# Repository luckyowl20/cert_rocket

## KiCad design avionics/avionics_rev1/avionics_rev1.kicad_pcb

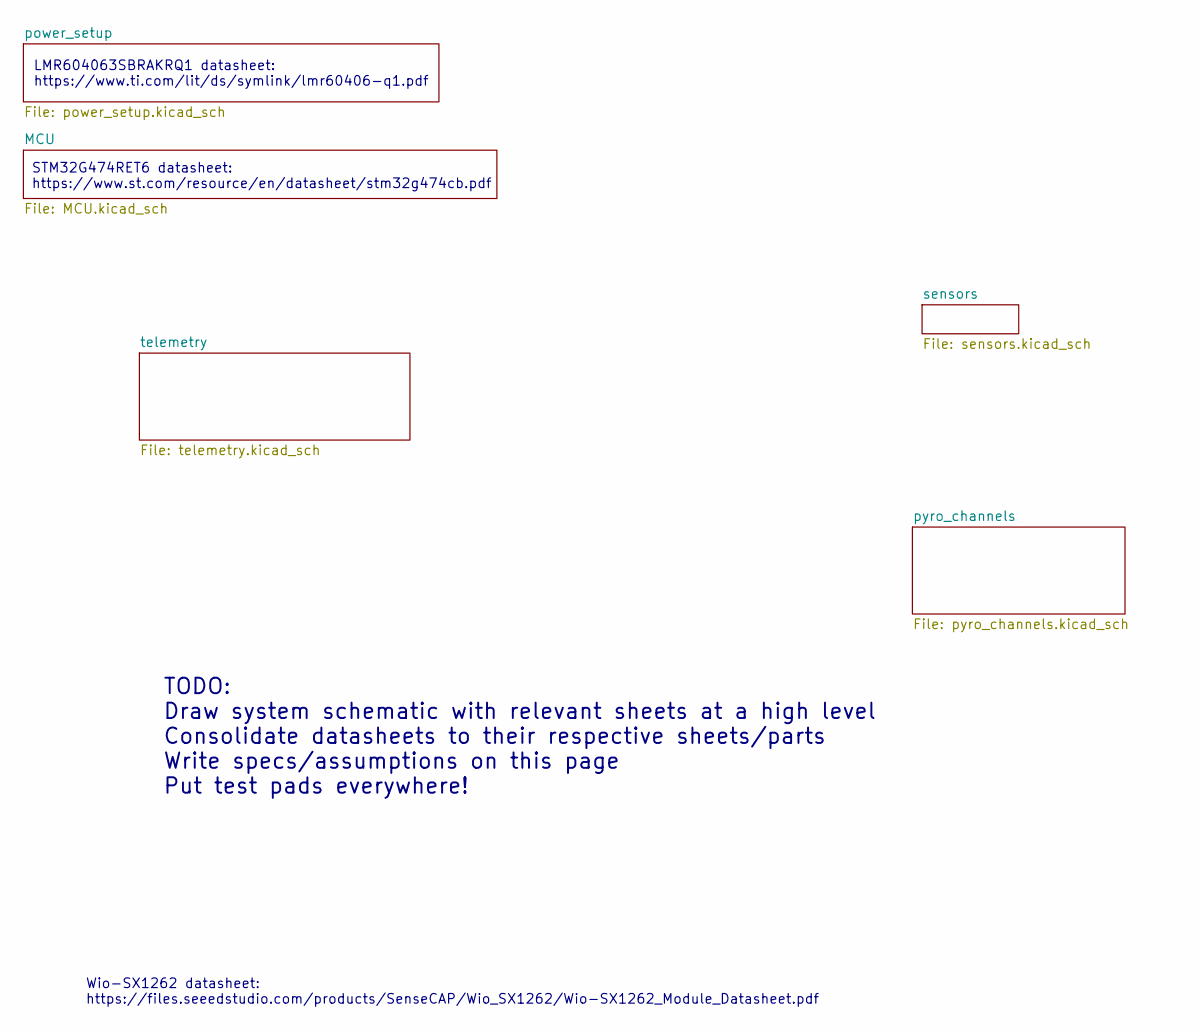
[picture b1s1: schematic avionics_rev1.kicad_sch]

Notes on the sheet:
Wio-SX1262 datasheet: https://files.seeedstudio.com/products/SenseCAP/Wio_SX1262/Wio-SX1262_Module_Datasheet.pdf
STM32G474RET6 datasheet: https://www.st.com/resource/en/datasheet/stm32g474cb.pdf
LMR604063SBRAKRQ1 datasheet: https://www.ti.com/lit/ds/symlink/lmr60406-q1.pdf
TODO: Draw system schematic with relevant sheets at a high level Consolidate datasheets to their respective sheets/parts Write specs/assumptions on this page Put test pads everywhere!

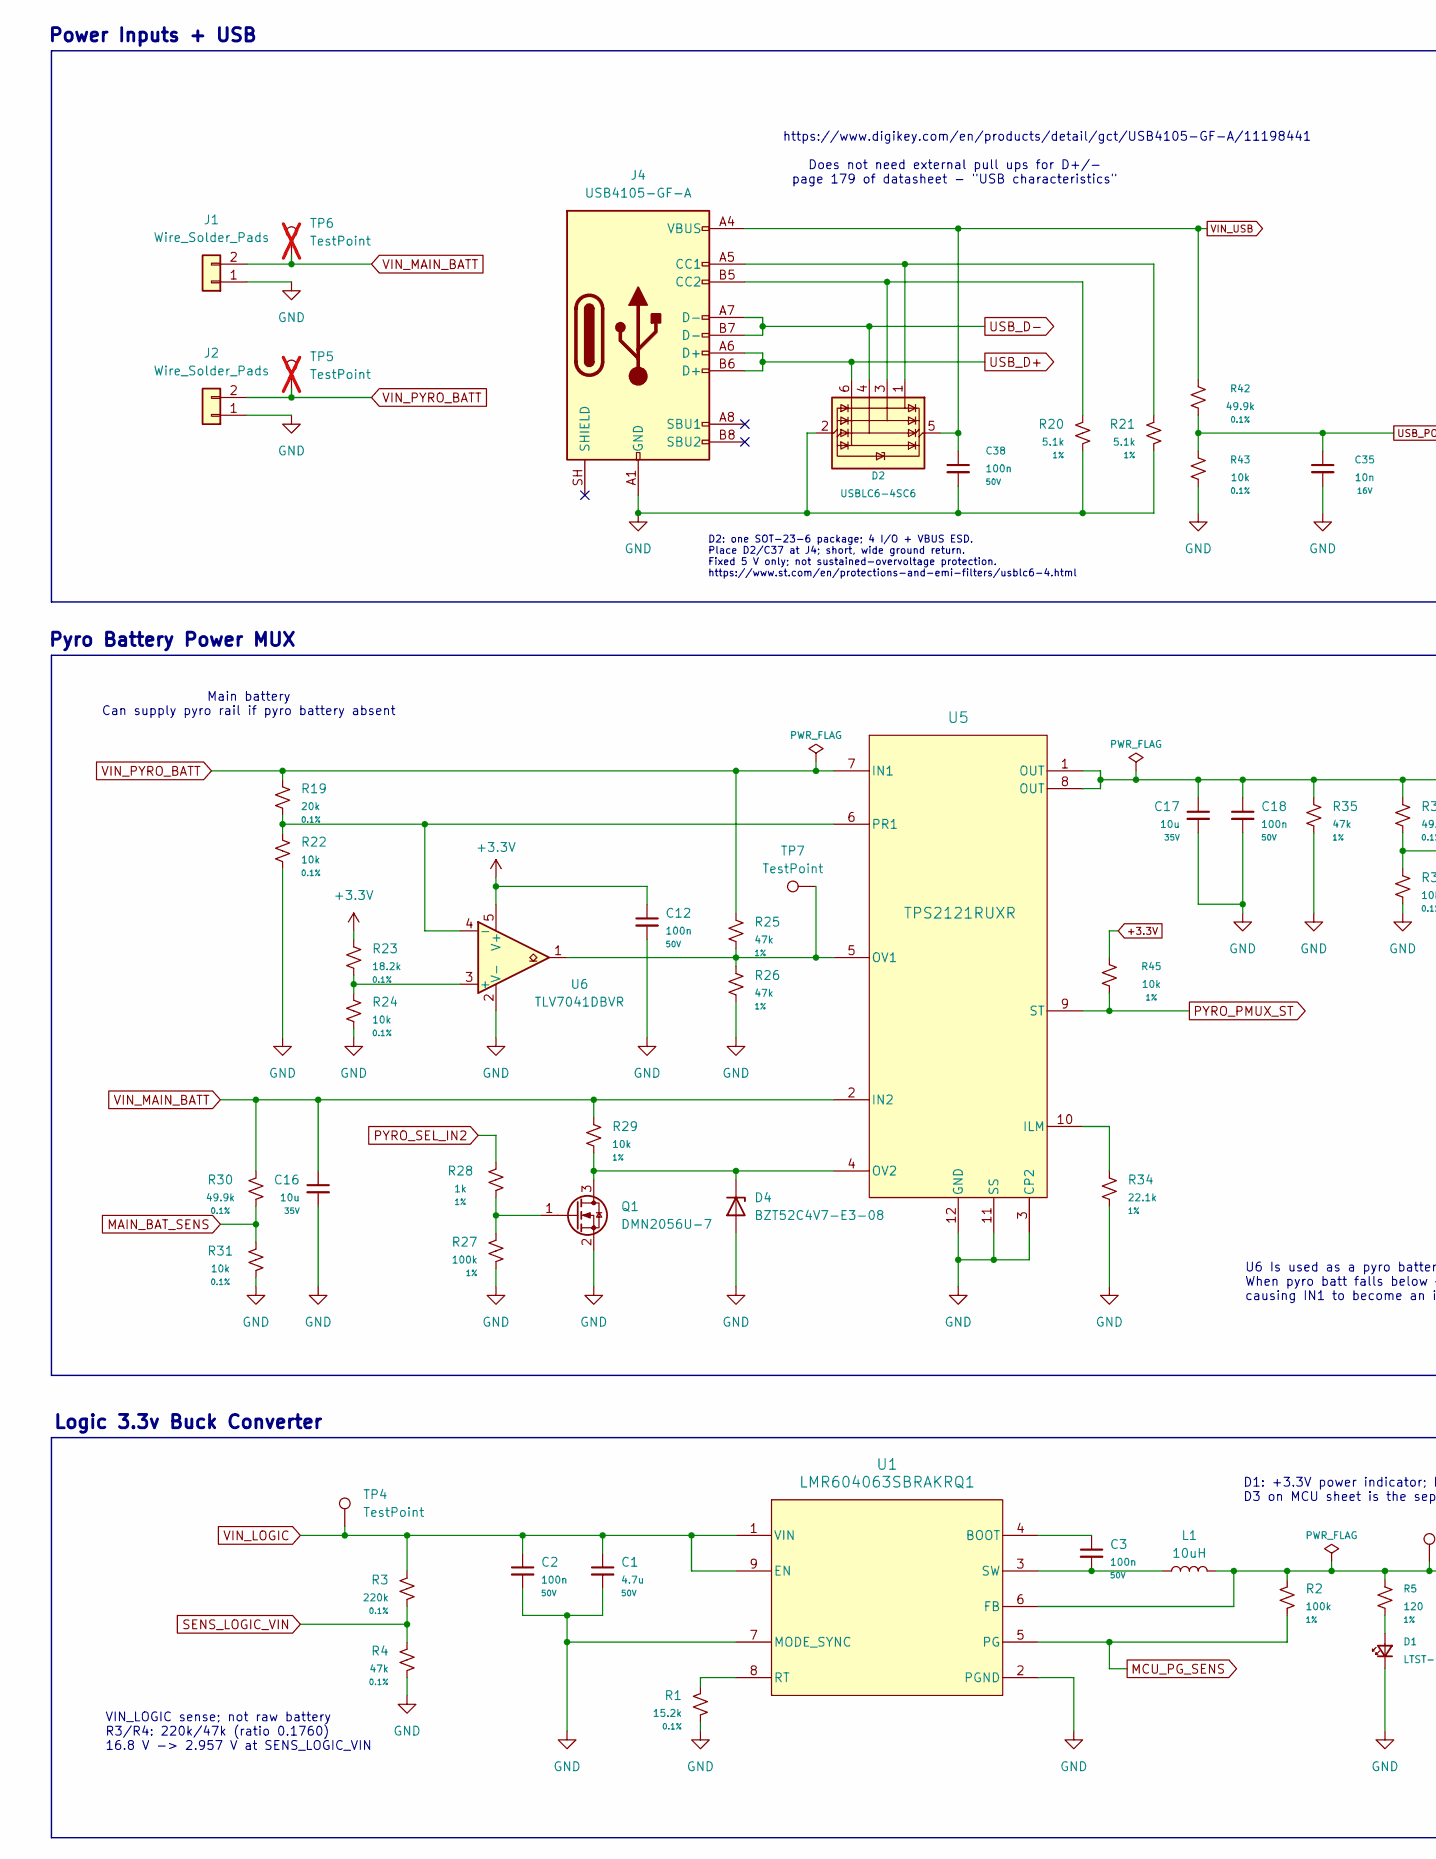
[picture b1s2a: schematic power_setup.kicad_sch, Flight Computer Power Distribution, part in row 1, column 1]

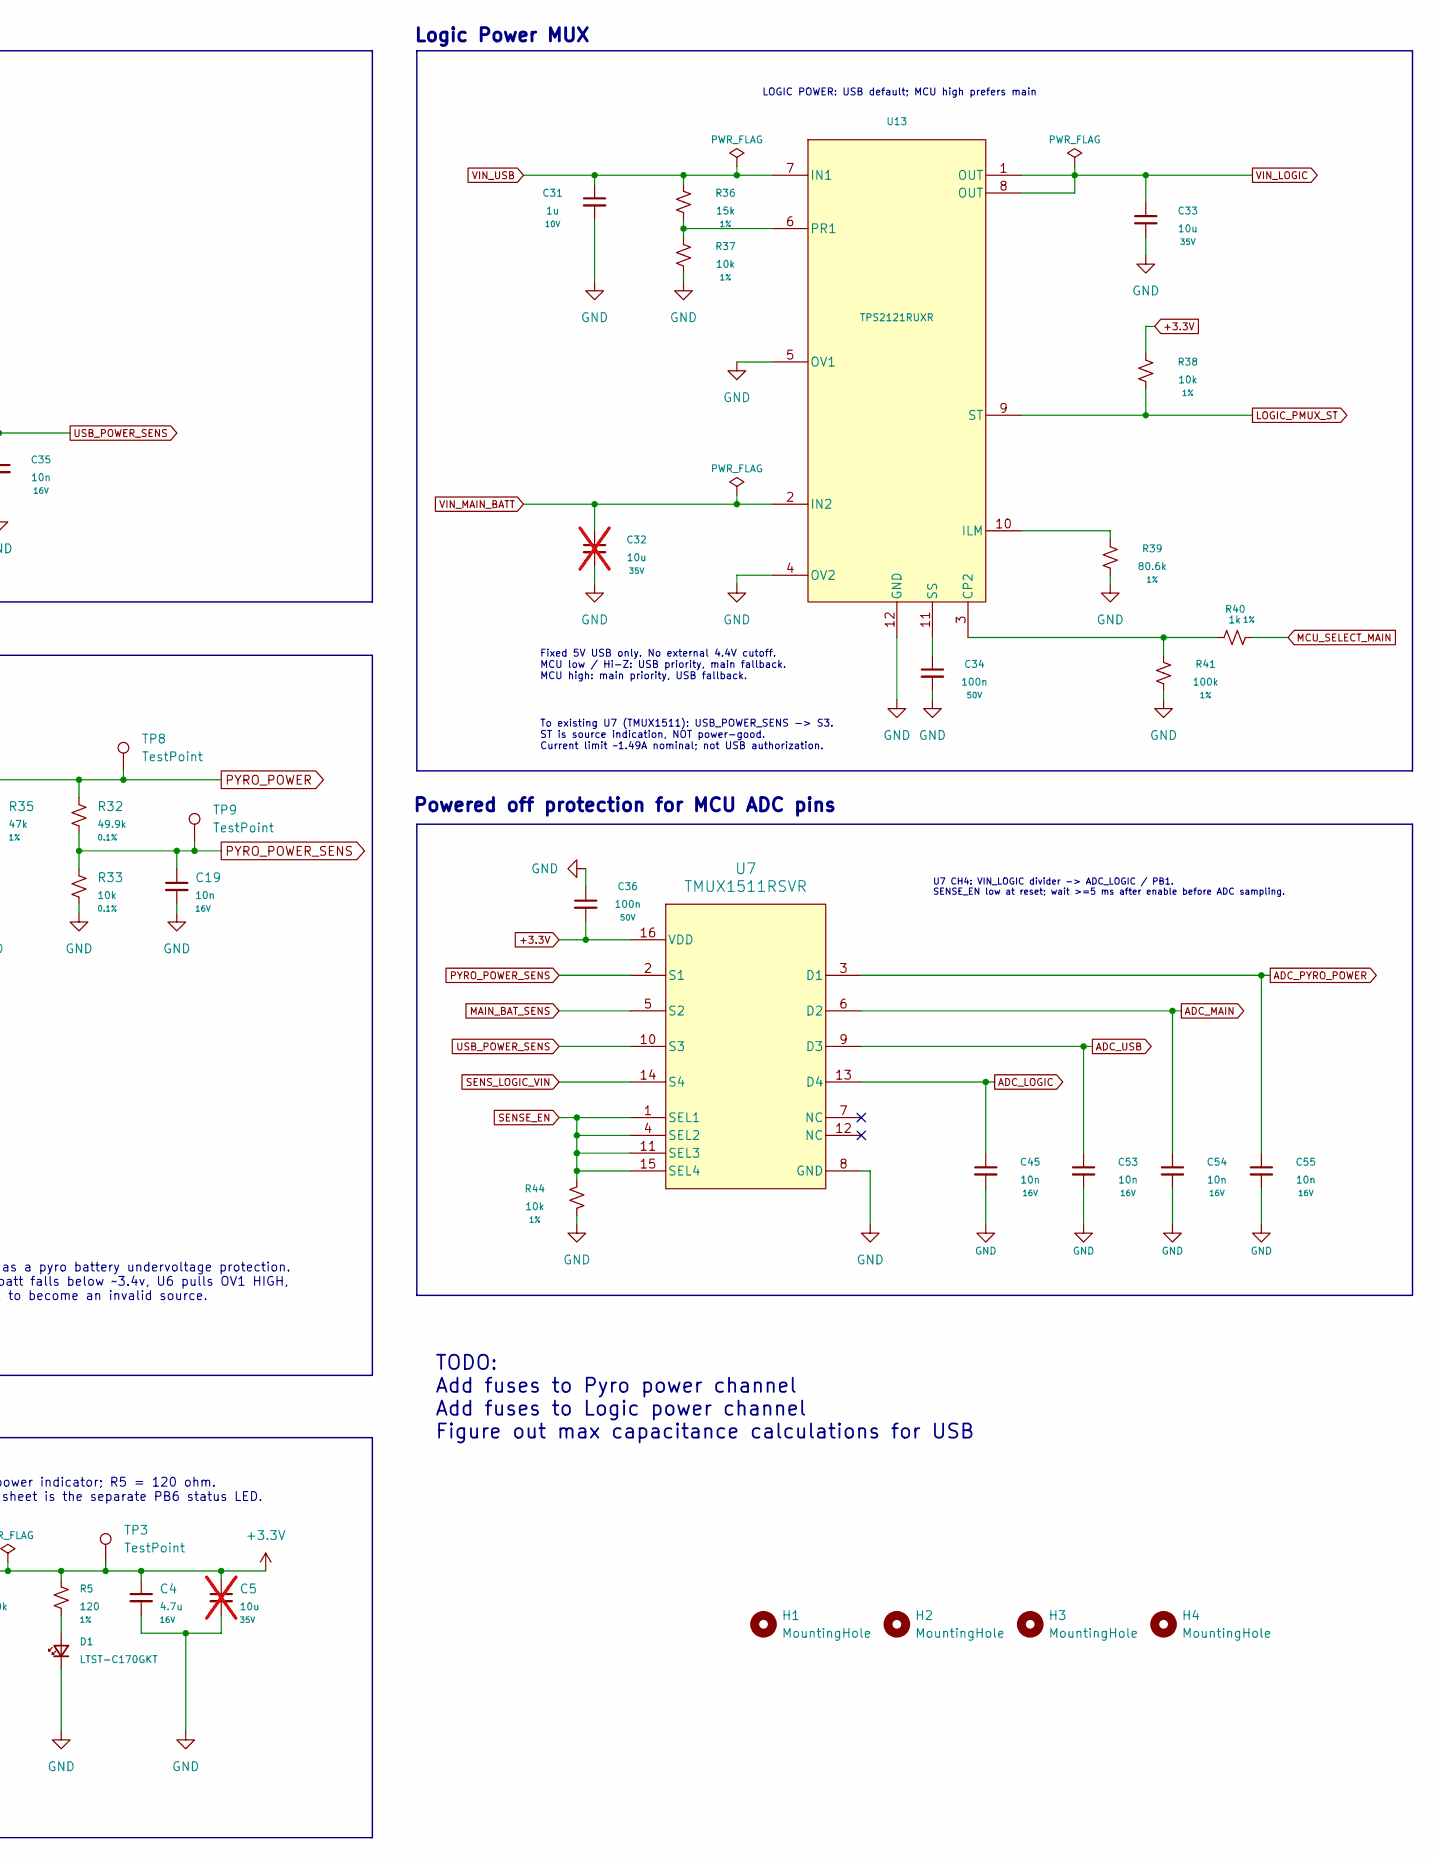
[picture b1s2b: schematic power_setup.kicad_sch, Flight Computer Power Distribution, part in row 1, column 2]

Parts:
C1: 4.7u; C_0805_2012Metric; Voltage 50V; Tolerance 10%; MPN C2012X5R1H475K125AB
C2, C3, C12, C18, C34, C36, C38: 100n; C_0603_1608Metric; Voltage 50V; Tolerance 10%; MPN C0603C104K5RACTU
C4: 4.7u; C_0603_1608Metric; Voltage 16V; Tolerance 10%; MPN GRM188R61C475KE11D
C5, C32: 10u; C_0805_2012Metric; Voltage 35V; Tolerance 10%; MPN GRM21BR6YA106KE43L; not fitted
C16, C17, C33: 10u; C_0805_2012Metric; Voltage 35V; Tolerance 10%; MPN GRM21BR6YA106KE43L
C19, C35: 10n; C_0603_1608Metric; Voltage 16V; Tolerance 10%; MPN CC0603KRX7R7BB103
C31: 1u; C_0603_1608Metric; Voltage 10V; Tolerance 10%; MPN C1608X7R1A105K080AC
C45, C53, C54, C55: 10n; C_0603_1608Metric; Tolerance 10%; Voltage 16V; MPN CC0603KRX7R7BB103
D1: LTST-C170GKT; LTST_C170GKT_0805; MPN LTST-C170GKT
D2: USBLC6-4SC6; USBLC6_4SC6_SOT23_6; MPN USBLC6-4SC6
D4: BZT52C4V7-E3-08; BZT52C4V7_E3_08_SOD123; MPN BZT52C4V7-E3-08
H1, H2, H3, H4: MountingHole; MountingHole_2.2mm_M2
J1, J2: Wire_Solder_Pads; WireSolderPads_1x02_3x2mm_P4mm
J4: USB4105-GF-A; USB_C_Receptacle_GCT_USB4105-xx-A_16P_TopMnt_Horizontal; MPN USB4105-GF-A
L1: 10uH; L_Changjiang_FTC303010D
Q1: DMN2056U-7; DMN2056U_7_SOT23; MPN DMN2056U-7
R1: 15.2k; R_0603_1608Metric; Tolerance 0.1%; Voltage 75V; MPN RN73R1JTTD1522B25
R2, R27, R41: 100k; R_0603_1608Metric; Tolerance 1%; Voltage 75V; MPN RC0603FR-07100KL
R3: 220k; R_0603_1608Metric; Tolerance 0.1%; Voltage 75V; MPN RT0603BRD07220KL
R4: 47k; R_0603_1608Metric; Tolerance 0.1%; Voltage 75V; MPN RT0603BRD0747KL
R5: 120; R_0603_1608Metric; Tolerance 1%; Voltage 75V; MPN RC0603FR-07120RL
R19: 20k; R_0603_1608Metric; Tolerance 0.1%; Voltage 75V; MPN RT0603BRD0720KL
R20, R21: 5.1k; R_0603_1608Metric; Tolerance 1%; Voltage 75V; MPN RC0603FR-075K1L
R22, R24, R31, R33, R43: 10k; R_0603_1608Metric; Tolerance 0.1%; Voltage 75V; MPN RT0603BRD0710KL
R23: 18.2k; R_0603_1608Metric; Tolerance 0.1%; Voltage 75V; MPN RT0603BRD0718K2L
R25, R26, R35: 47k; R_0603_1608Metric; Tolerance 1%; Voltage 75V; MPN RC0603FR-0747KL
R28, R40: 1k; R_0603_1608Metric; Tolerance 1%; Voltage 75V; MPN RC0603FR-071KL
R29, R37, R38, R44, R45: 10k; R_0603_1608Metric; Tolerance 1%; Voltage 75V; MPN RC0603FR-0710KL
R30, R32, R42: 49.9k; R_0603_1608Metric; Tolerance 0.1%; Voltage 75V; MPN RT0603BRD0749K9L
R34: 22.1k; R_0603_1608Metric; Tolerance 1%; Voltage 75V; MPN RC0603FR-0722K1L
R36: 15k; R_0603_1608Metric; Tolerance 1%; Voltage 75V; MPN RC0603FR-0715KL
R39: 80.6k; R_0603_1608Metric; Tolerance 1%; Voltage 75V; MPN RC0603FR-0780K6L
TP3, TP4, TP7, TP8, TP9: TestPoint; TestPoint_Pad_D1.0mm
TP5, TP6: TestPoint; TestPoint_Pad_D1.0mm; not fitted
U1: LMR604063SBRAKRQ1; LMR604063SBRAKRQ1_RAK9; MPN LMR604063SBRAKRQ1
U5, U13: TPS2121RUXR; TPS2121RUXR_RUX12; MPN TPS2121RUXR
U6: TLV7041DBVR; TLV7041DBVR_SOT23_5; MPN TLV7041DBVR
U7: TMUX1511RSVR; TMUX1511RSVR_RSV16; MPN TMUX1511RSVR

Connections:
ADC_LOGIC: C45.1, U7.13 (D4); also elsewhere on the board
ADC_MAIN: C54.1, U7.6 (D2); also elsewhere on the board
ADC_PYRO_POWER: C55.1, U7.3 (D1); also elsewhere on the board
ADC_USB: C53.1, U7.9 (D3); also elsewhere on the board
GND: C1.2, C2.2, C4.2, C5.2, C12.2, C16.2, C17.2, C18.2, C19.2, C31.2, C32.2, C33.2, C34.2, C35.2, C36.1, C38.2, C45.2, C53.2, C54.2, C55.2, D1.1 (K), D2.2 (GND), D4.2 (A), J1.1, J2.1, J4.A1 (GND), J4.A12 (GND), J4.B1 (GND), J4.B12 (GND), Q1.2 (S), R1.1, R4.1, R20.1, R21.1, R22.2, R24.2, R26.2, R27.2, R31.2, R33.2, R34.2, R35.2, R37.2, R39.2, R41.2, R43.2, R44.2, U1.2 (PGND), U1.7 (MODE_SYNC), U5.3 (CP2), U5.11 (SS), U5.12 (GND), U6.2 (V-), U7.8 (GND), U13.4 (OV2), U13.5 (OV1), U13.12 (GND); also elsewhere on the board
LOGIC_PMUX_ST: R38.2, U13.9 (ST); also elsewhere on the board
MAIN_BAT_SENS: R30.2, R31.1, U7.5 (S2)
MCU_PG_SENS: R2.2, U1.5 (PG); also elsewhere on the board
MCU_SELECT_MAIN: R40.2; also elsewhere on the board
unnamed: D1.2 (A), R5.1
unnamed: D2.1 (I/O1), J4.A5 (CC1), R21.2
unnamed: D2.3 (I/O2), J4.B5 (CC2), R20.2
unnamed: D4.1 (K), Q1.3 (D), R29.1, U5.4 (OV2)
unnamed: Q1.1 (G), R27.1, R28.2
unnamed: C3.1, U1.4 (BOOT)
unnamed: R1.2, U1.8 (RT)
unnamed: C3.2, L1.1, U1.3 (SW)
unnamed: R34.1, U5.10 (ILM)
unnamed: R25.2, R26.1, TP7.1 (1_1), U5.5 (OV1), U6.1
unnamed: R19.2, R22.1, U5.6 (PR1), U6.4 (-)
unnamed: R23.2, R24.1, U6.3 (+)
unnamed: R40.1, R41.1, U13.3 (CP2)
unnamed: R39.1, U13.10 (ILM)
unnamed: R36.2, R37.1, U13.6 (PR1)
unnamed: C34.1, U13.11 (SS)
PYRO_PMUX_ST: R45.2, U5.9 (ST); also elsewhere on the board
PYRO_POWER_SENS: C19.1, R32.2, R33.1, TP9.1 (1_1), U7.2 (S1)
PYRO_SEL_IN2: R28.1; also elsewhere on the board
SENSE_EN: R44.1, U7.1 (SEL1), U7.4 (SEL2), U7.11 (SEL3), U7.15 (SEL4); also elsewhere on the board
SENS_LOGIC_VIN: R3.1, R4.2, U7.14 (S4)
USB_D+: D2.6 (I/O4), J4.A6 (D+), J4.B6 (D+); also elsewhere on the board
USB_D-: D2.4 (I/O3), J4.A7 (D-), J4.B7 (D-); also elsewhere on the board
USB_POWER_SENS: C35.1, R42.2, R43.1, U7.10 (S3)

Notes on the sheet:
Logic 3.3v Buck Converter
Power Inputs + USB
TODO: Add fuses to Pyro power channel Add fuses to Logic power channel Figure out max capacitance calculations for USB
LOGIC POWER: USB default; MCU high prefers main
https://www.digikey.com/en/products/detail/gct/USB4105-GF-A/11198441
Fixed 5V USB only. No external 4.4V cutoff. MCU low / Hi-Z: USB priority, main fallback. MCU high: main priority, USB fallback.
Pyro Battery Power MUX
Does not need external pull ups for D+/- page 179 of datasheet - "USB characteristics"
U6 Is used as a pyro battery undervoltage protection. When pyro batt falls below ~3.4v, U6 pulls OV1 HIGH, causing IN1 to become an invalid source.
U7 CH4: VIN_LOGIC divider -> ADC_LOGIC / PB1. SENSE_EN low at reset; wait >=5 ms after enable before ADC sampling.
VIN_LOGIC sense; not raw battery R3/R4: 220k/47k (ratio 0.1760) 16.8 V -> 2.957 V at SENS_LOGIC_VIN
D2: one SOT-23-6 package; 4 I/O + VBUS ESD. Place D2/C37 at J4; short, wide ground return. Fixed 5 V only; not sustained-overvoltage protection. https://www.st.com/en/protections-and-emi-filters/usblc6-4.html
D1: +3.3V power indicator; R5 = 120 ohm. D3 on MCU sheet is the separate PB6 status LED.
Powered off protection for MCU ADC pins
To existing U7 (TMUX1511): USB_POWER_SENS -> S3. ST is source indication, NOT power-good. Current limit ~1.49A nominal; not USB authorization.
Main battery Can supply pyro rail if pyro battery absent
Logic Power MUX

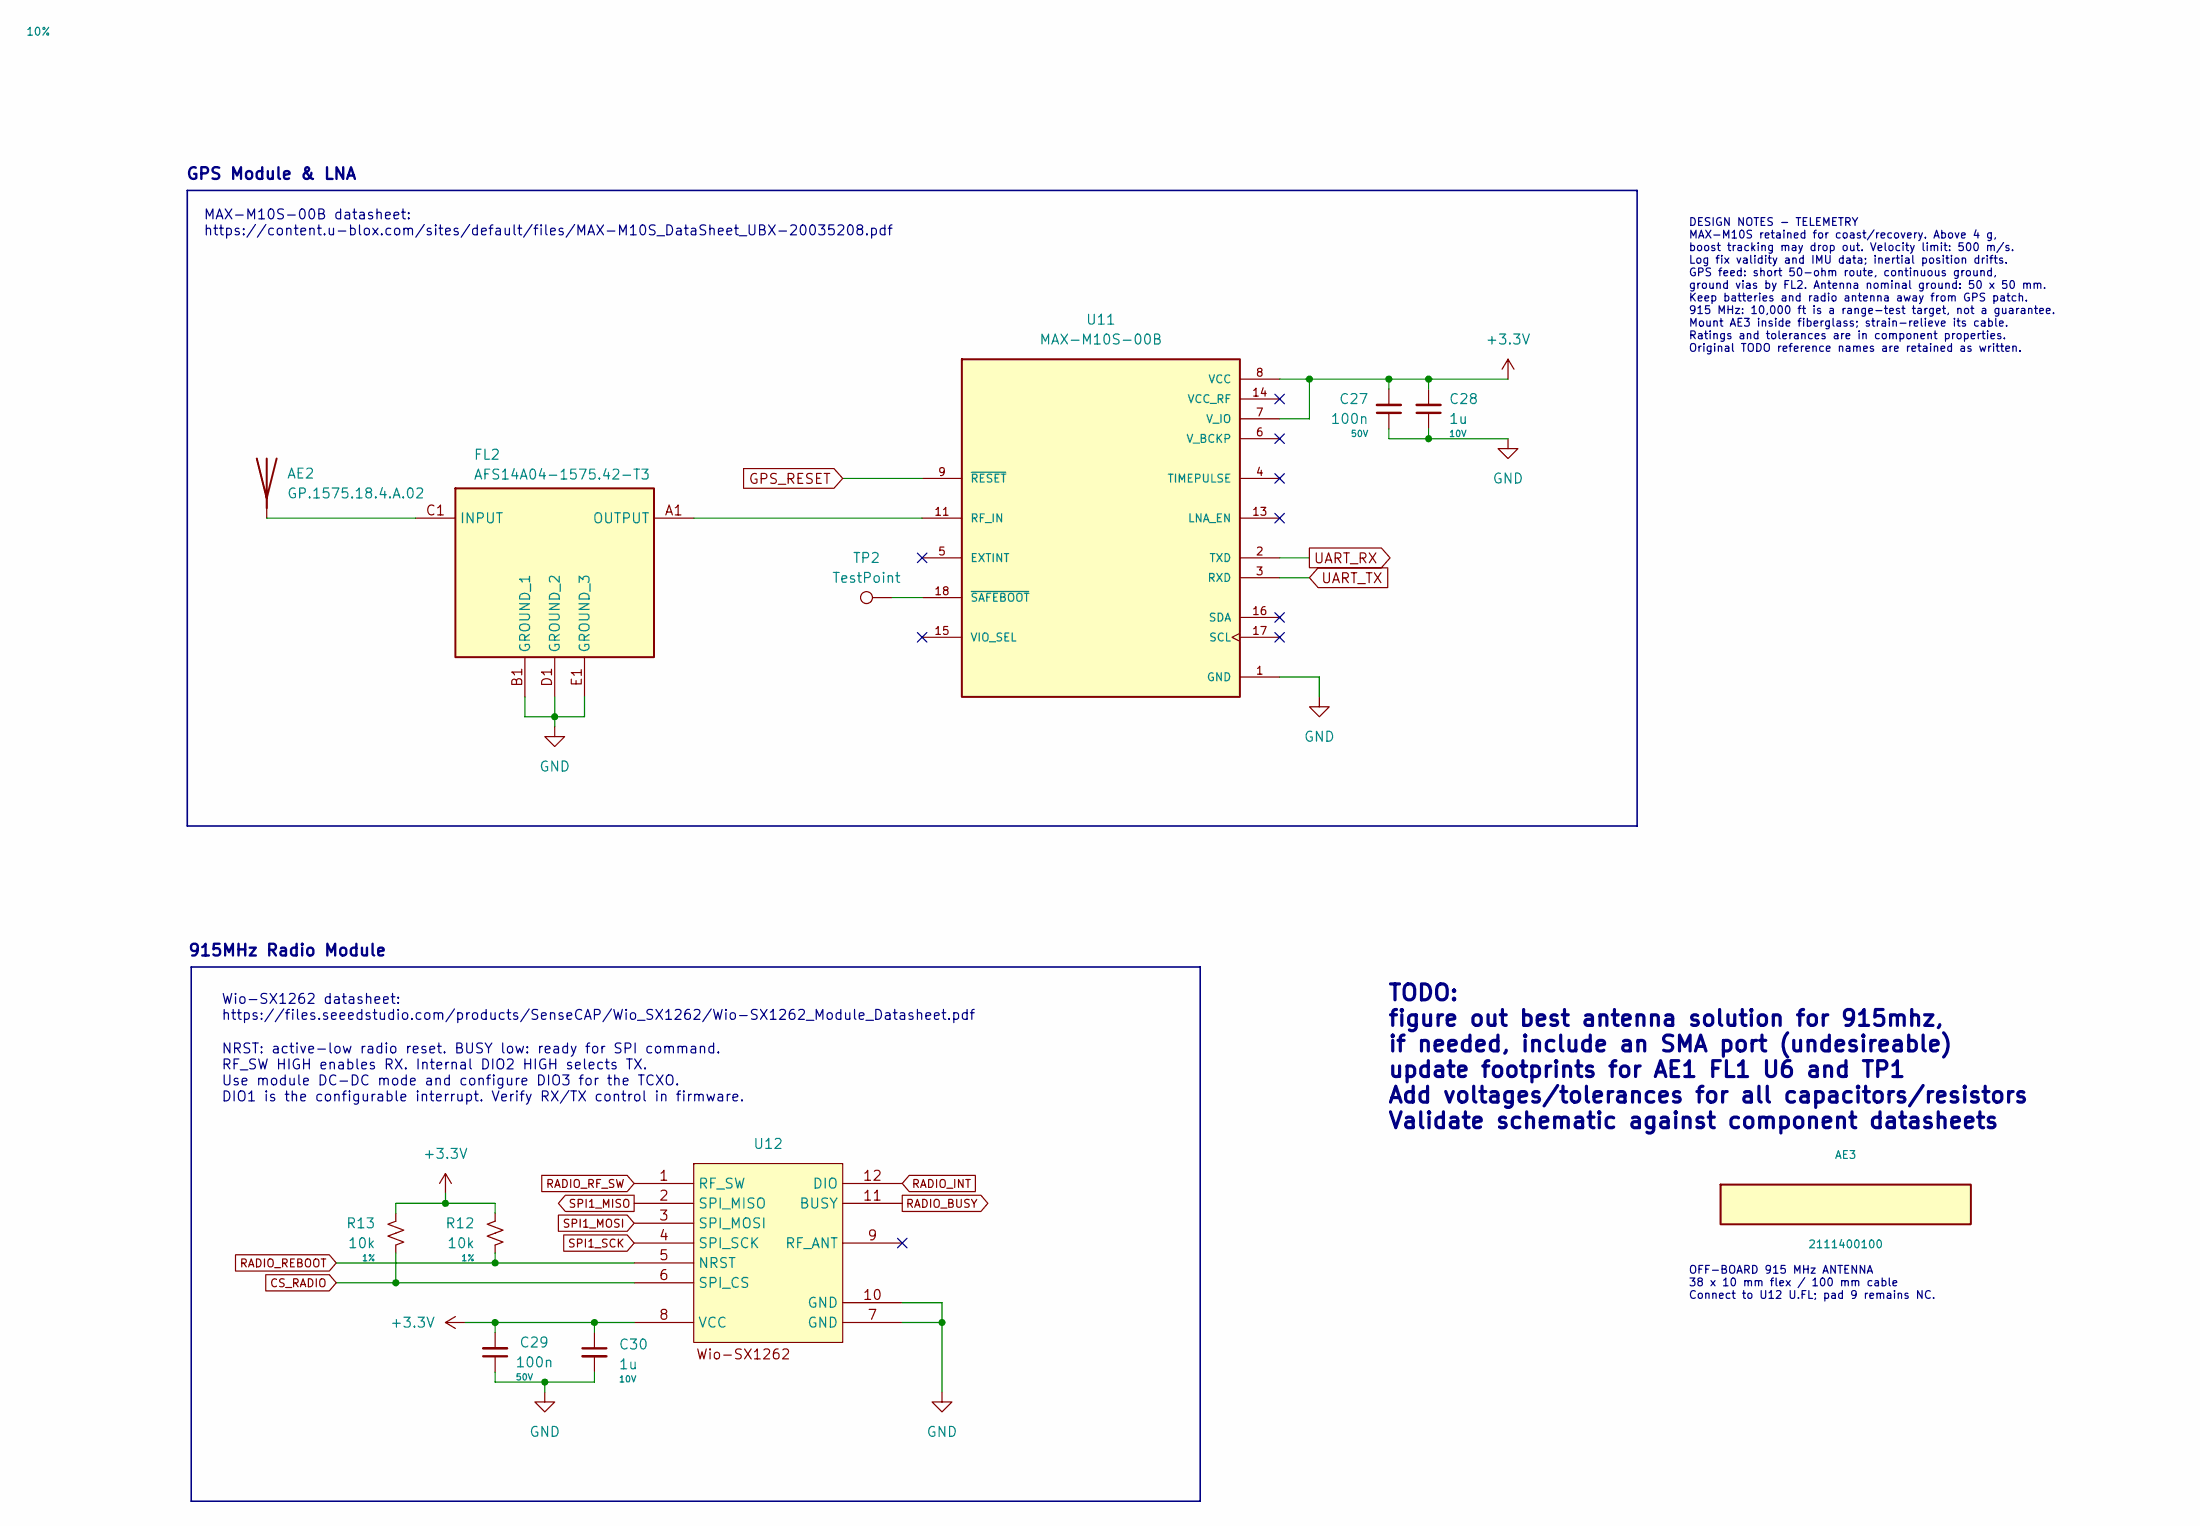
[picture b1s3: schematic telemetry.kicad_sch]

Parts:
AE2: GP.1575.18.4.A.02; ANT_GP.1575.18.4.A.02_TAL; MPN GP.1575.18.4.A.02
AE3: 2111400100; MPN 2111400100
C27, C29: 100n; C_0603_1608Metric; Tolerance 10%; Voltage 50V; MPN C0603C104K5RACTU
C28, C30: 1u; C_0603_1608Metric; Tolerance 10%; Voltage 10V; MPN C1608X7R1A105K080AC
FL2: AFS14A04-1575.42-T3; AFS14A04157542T3; Mouser Part Number 815-AFS14A04-1575-T3
R12, R13: 10k; R_0603_1608Metric; Tolerance 1%; Voltage 75V; MPN RC0603FR-0710KL
TP2: TestPoint; TestPoint_Pad_D1.0mm
U11: MAX-M10S-00B; XCVR_MAX-M10S-00B; PARTREV C1
U12: Wio-SX1262; WIO-SX1262; MPN 114993390

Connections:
CS_RADIO: R13.1, U12.6 (SPI_CS); also elsewhere on the board
GND: C27.1, C28.1, C29.1, C30.2, FL2.B1 (GROUND_1), FL2.D1 (GROUND_2), FL2.E1 (GROUND_3), U11.1 (GND), U11.10 (GND), U11.12 (GND), U12.7 (GND), U12.10 (GND); also elsewhere on the board
GPS_RESET: U11.9 (~RESET); also elsewhere on the board
unnamed: AE2.1 (A_1), FL2.C1 (INPUT)
unnamed: FL2.A1 (OUTPUT), U11.11 (RF_IN)
unnamed: TP2.1 (1_1), U11.18 (~SAFEBOOT)
RADIO_BUSY: U12.11 (BUSY); also elsewhere on the board
RADIO_INT: U12.12 (DIO); also elsewhere on the board
RADIO_REBOOT: R12.1, U12.5 (NRST); also elsewhere on the board
RADIO_RF_SW: U12.1 (RF_SW); also elsewhere on the board
SPI1_MISO: U12.2 (SPI_MISO); also elsewhere on the board
SPI1_MOSI: U12.3 (SPI_MOSI); also elsewhere on the board
SPI1_SCK: U12.4 (SPI_SCK); also elsewhere on the board
UART_RX: U11.2 (TXD); also elsewhere on the board
UART_TX: U11.3 (RXD); also elsewhere on the board

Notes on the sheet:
DESIGN NOTES - TELEMETRY MAX-M10S retained for coast/recovery. Above 4 g, boost tracking may drop out. Velocity limit: 500 m/s. Log fix validity and IMU data; inertial position drifts. GPS feed: short 50-ohm route, continuous ground, ground vias by FL2. Antenna nominal ground: 50 x 50 mm. Keep batt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
TODO: figure out best antenna solution for 915mhz, if needed, include an SMA port (undesireable) update footprints for AE1 FL1 U6 and TP1 Add voltages/tolerances for all capacitors/resistors Validate schematic against component datasheets
GPS Module & LNA
NRST: active-low radio reset. BUSY low: ready for SPI command. RF_SW HIGH enables RX. Internal DIO2 HIGH selects TX. Use module DC-DC mode and configure DIO3 for the TCXO. DIO1 is the configurable interrupt. Verify RX/TX control in firmware.
Wio-SX1262 datasheet: https://files.seeedstudio.com/products/SenseCAP/Wio_SX1262/Wio-SX1262_Module_Datasheet.pdf
OFF-BOARD 915 MHz ANTENNA 38 x 10 mm flex / 100 mm cable Connect to U12 U.FL; pad 9 remains NC.
MAX-M10S-00B datasheet: https://content.u-blox.com/sites/default/files/MAX-M10S_DataSheet_UBX-20035208.pdf
915MHz Radio Module

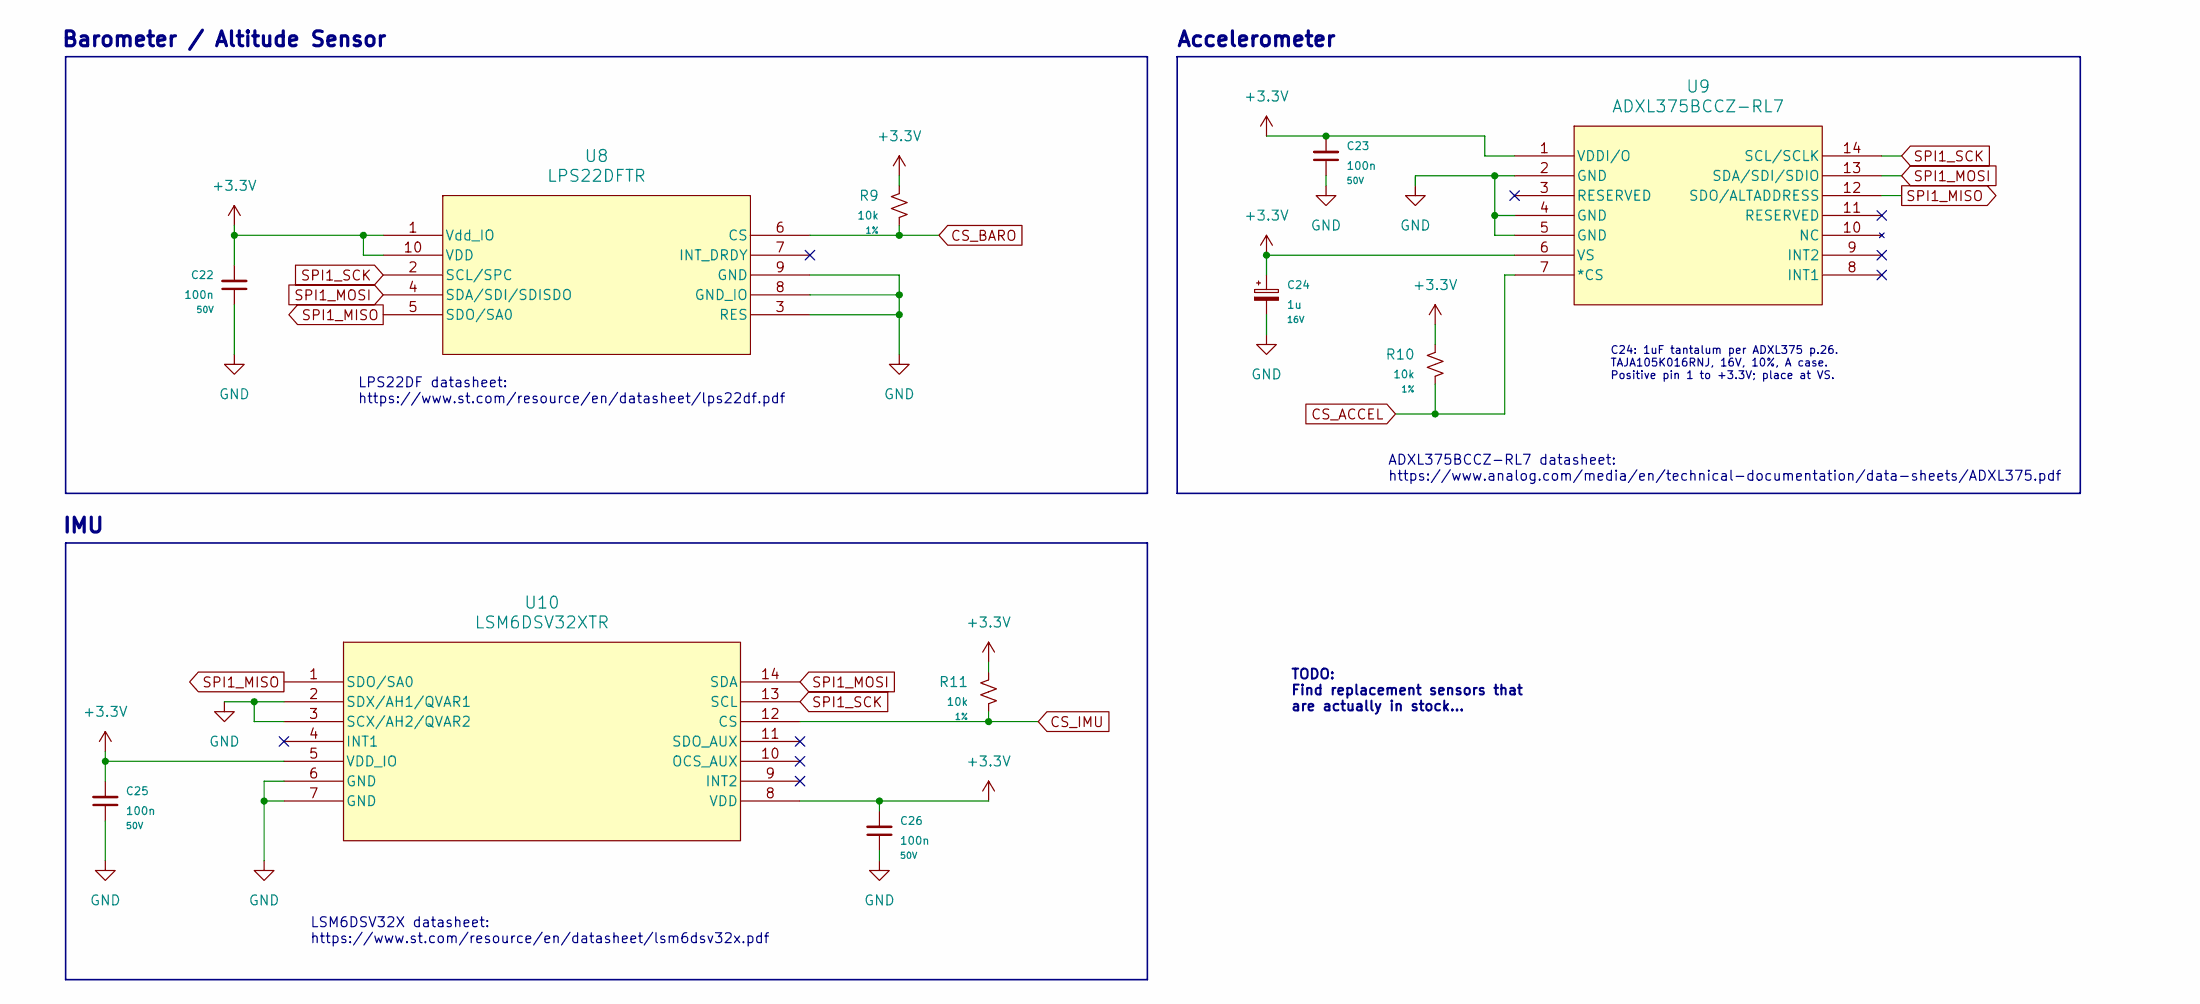
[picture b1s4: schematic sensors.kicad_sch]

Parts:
C22, C23, C25, C26: 100n; C_0603_1608Metric; Tolerance 10%; Voltage 50V; MPN C0603C104K5RACTU
C24: 1u; TAJA105K016RNJ_3216_18; Tolerance 10%; Voltage 16V; MPN TAJA105K016RNJ
R9, R10, R11: 10k; R_0603_1608Metric; Tolerance 1%; Voltage 75V; MPN RC0603FR-0710KL
U8: LPS22DFTR; QFN_22DFTR_STM; MPN LPS22DFTR
U9: ADXL375BCCZ-RL7; LGA_CC-14-1_ADI; MPN ADXL375BCCZ-RL7
U10: LSM6DSV32XTR; LGA-14L_2p5X3p0X0p86_STM; MPN LSM6DSV32XTR

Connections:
CS_ACCEL: R10.1, U9.7 (*CS); also elsewhere on the board
CS_BARO: R9.1, U8.6 (CS); also elsewhere on the board
CS_IMU: R11.1, U10.12 (CS); also elsewhere on the board
GND: C22.1, C23.1, C24.2, C25.1, C26.1, U8.3 (RES), U8.8 (GND_IO), U8.9 (GND), U9.2 (GND), U9.4 (GND), U9.5 (GND), U10.2 (SDX/AH1/QVAR1), U10.3 (SCX/AH2/QVAR2), U10.6 (GND), U10.7 (GND); also elsewhere on the board
SPI1_MISO: U8.5 (SDO/SA0), U9.12 (SDO/ALTADDRESS), U10.1 (SDO/SA0); also elsewhere on the board
SPI1_MOSI: U8.4 (SDA/SDI/SDISDO), U9.13 (SDA/SDI/SDIO), U10.14 (SDA); also elsewhere on the board
SPI1_SCK: U8.2 (SCL/SPC), U9.14 (SCL/SCLK), U10.13 (SCL); also elsewhere on the board

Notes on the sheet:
C24: 1uF tantalum per ADXL375 p.26. TAJA105K016RNJ, 16V, 10%, A case. Positive pin 1 to +3.3V; place at VS.
IMU
Barometer / Altitude Sensor
LSM6DSV32X datasheet: https://www.st.com/resource/en/datasheet/lsm6dsv32x.pdf
ADXL375BCCZ-RL7 datasheet: https://www.analog.com/media/en/technical-documentation/data-sheets/ADXL375.pdf
Accelerometer
TODO: Find replacement sensors that are actually in stock...
LPS22DF datasheet: https://www.st.com/resource/en/datasheet/lps22df.pdf

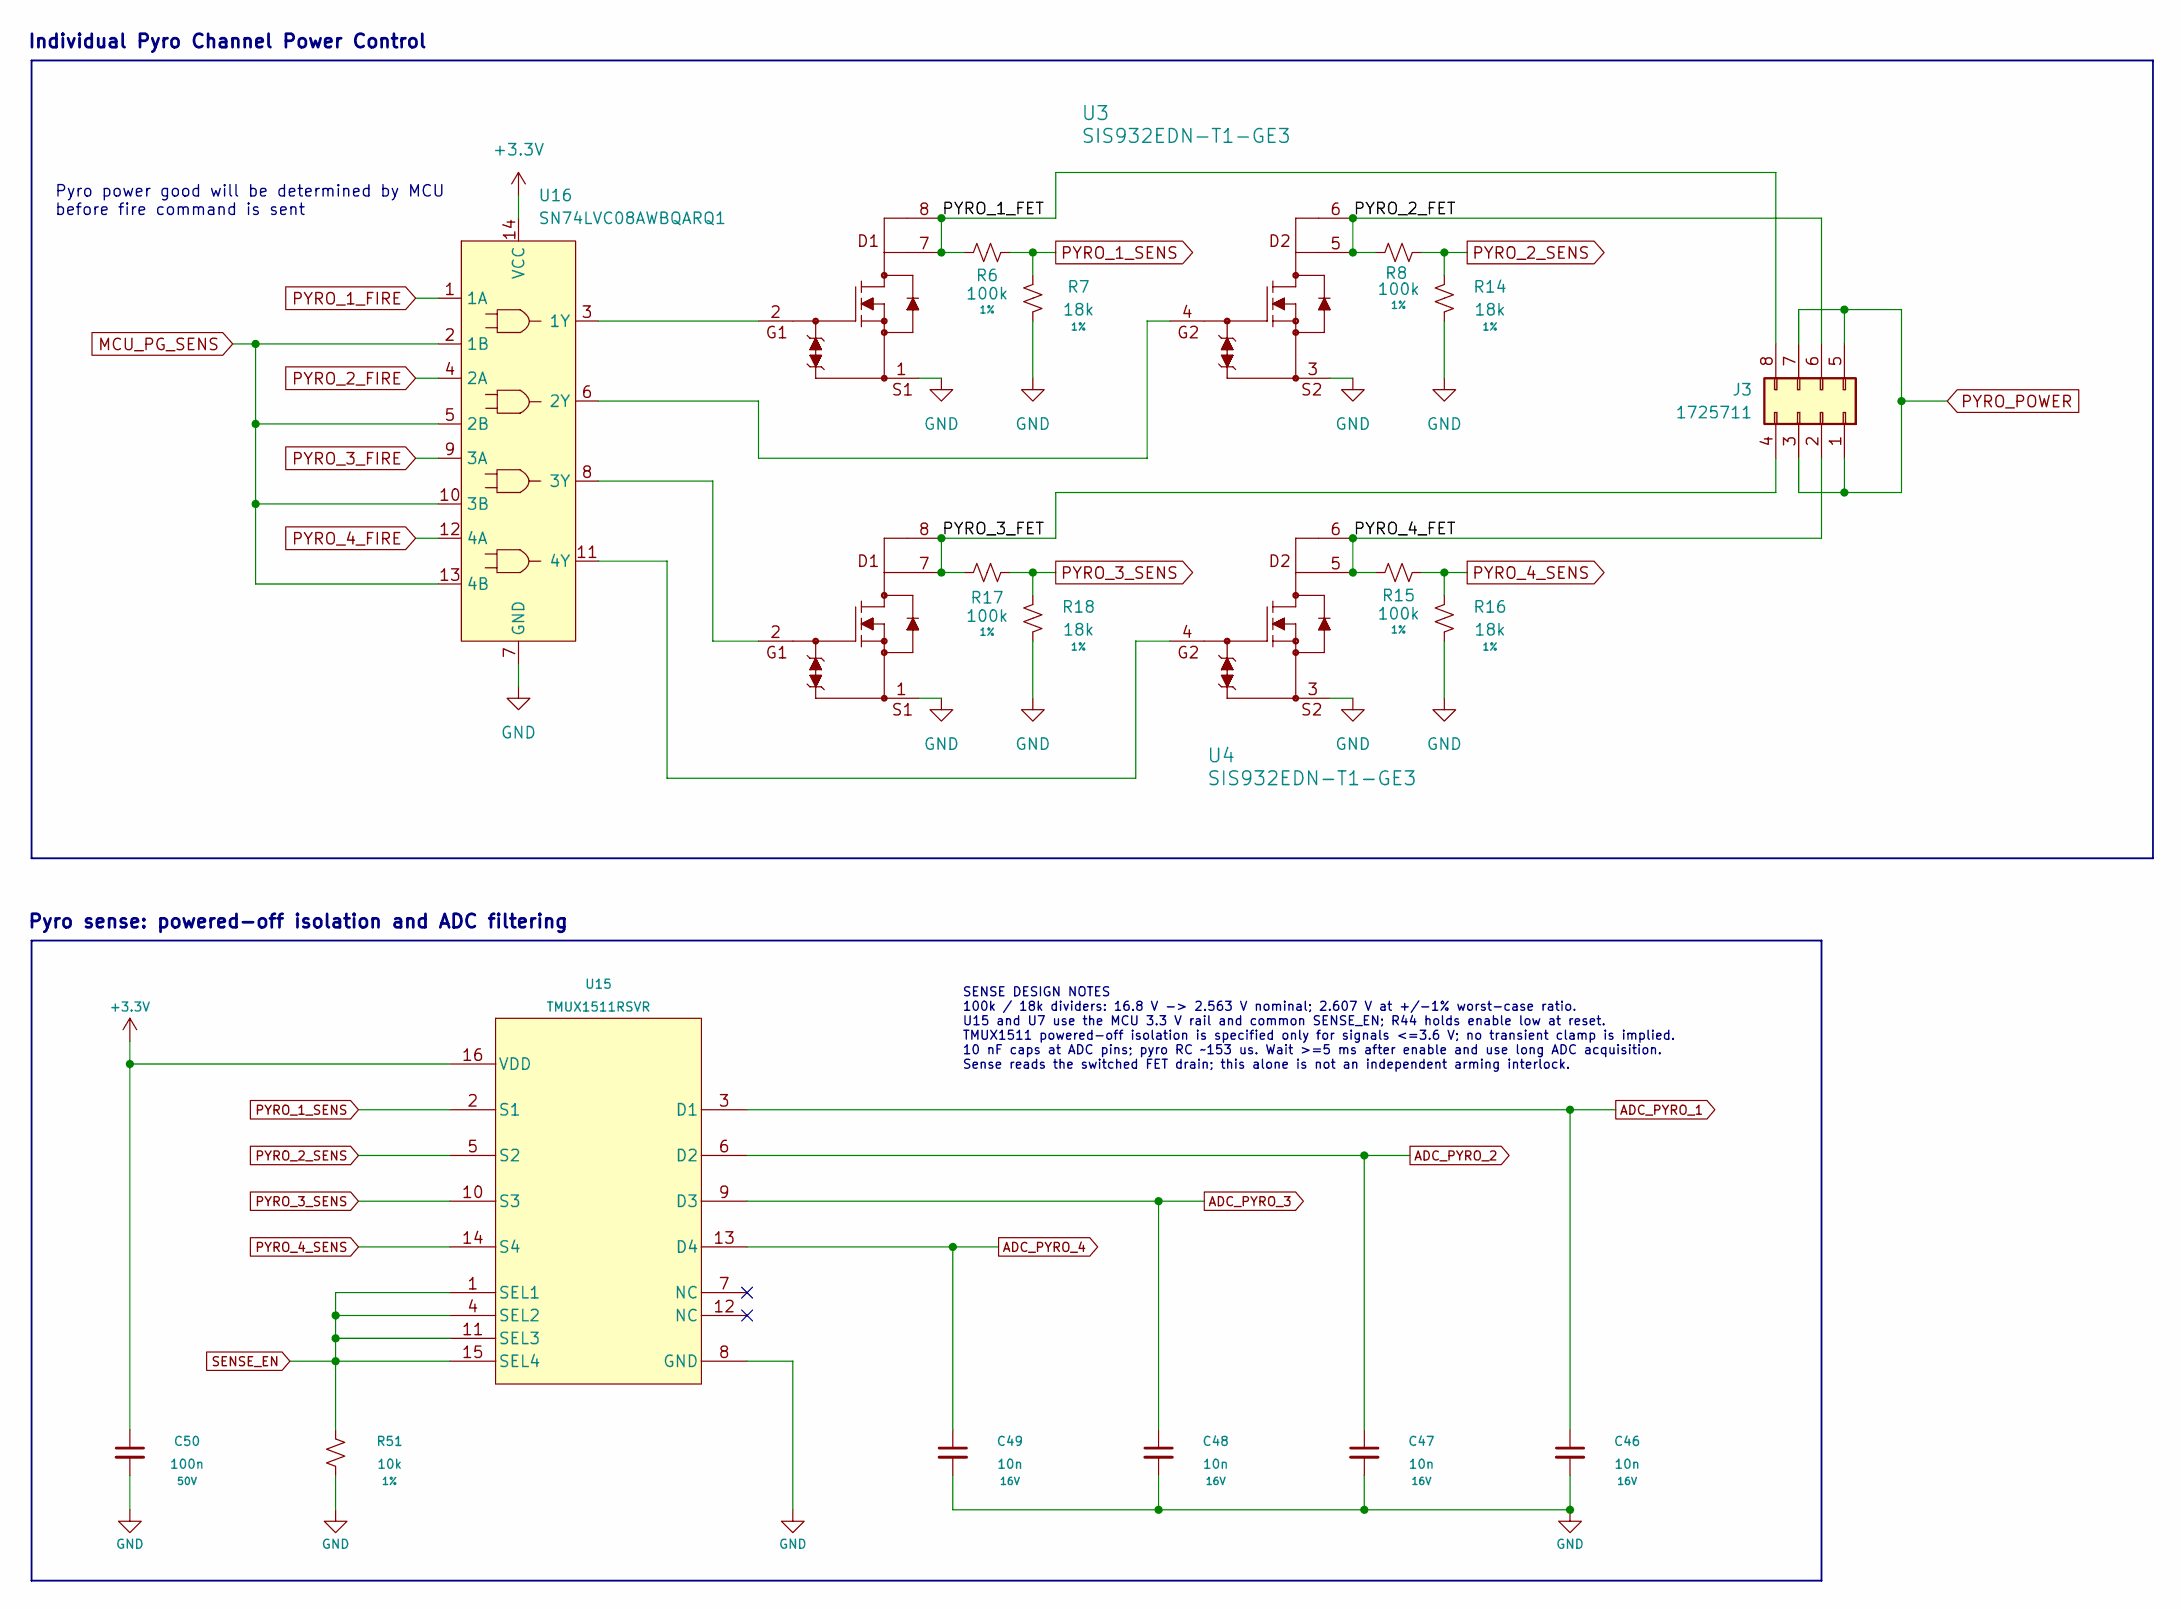
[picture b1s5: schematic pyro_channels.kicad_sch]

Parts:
C46, C47, C48, C49: 10n; C_0603_1608Metric; Tolerance 10%; Voltage 16V; MPN CC0603KRX7R7BB103
C50: 100n; C_0603_1608Metric; Tolerance 10%; Voltage 50V; MPN C0603C104K5RACTU
J3: 1725711; Phoenix_1725711_MPT_0.5_8_2.54; Current Rating 6A; MPN 1725711; DigiKey Part Number 277-1279-ND
R6, R8, R15, R17: 100k; R_0603_1608Metric; Tolerance 1%; Voltage 75V; MPN RC0603FR-07100KL
R7, R14, R16, R18: 18k; R_0603_1608Metric; Tolerance 1%; Voltage 75V; MPN RC0603FR-0718KL
R51: 10k; R_0603_1608Metric; Tolerance 1%; Voltage 75V; MPN RC0603FR-0710KL
U3, U4: SIS932EDN-T1-GE3; SIS932EDN_PowerPAK1212_8_Dual; MPN SIS932EDN-T1-GE3
U15: TMUX1511RSVR; TMUX1511RSVR_RSV16; MPN TMUX1511RSVR
U16: SN74LVC08AWBQARQ1; SN74LVC08AWBQARQ1_BQA14; MPN SN74LVC08AWBQARQ1

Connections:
/pyro_channels/PYRO_1_FET: J3.8, R6.2, U3.7, U3.8
/pyro_channels/PYRO_2_FET: J3.6, R8.2, U3.5, U3.6
/pyro_channels/PYRO_3_FET: J3.4, R17.2, U4.7, U4.8
/pyro_channels/PYRO_4_FET: J3.2, R15.2, U4.5, U4.6
ADC_PYRO_1: C46.1, U15.3 (D1); also elsewhere on the board
ADC_PYRO_2: C47.1, U15.6 (D2); also elsewhere on the board
ADC_PYRO_3: C48.1, U15.9 (D3); also elsewhere on the board
ADC_PYRO_4: C49.1, U15.13 (D4); also elsewhere on the board
GND: C46.2, C47.2, C48.2, C49.2, C50.2, R7.1, R14.1, R16.1, R18.1, R51.2, U3.1, U3.3, U4.1, U4.3, U15.8 (GND), U16.7 (GND), U16.15 (EP); also elsewhere on the board
MCU_PG_SENS: U16.2 (1B), U16.5 (2B), U16.10 (3B), U16.13 (4B); also elsewhere on the board
unnamed: U3.2, U16.3 (1Y)
unnamed: U3.4, U16.6 (2Y)
unnamed: U4.2, U16.8 (3Y)
unnamed: U4.4, U16.11 (4Y)
PYRO_1_FIRE: U16.1 (1A); also elsewhere on the board
PYRO_1_SENS: R6.1, R7.2, U15.2 (S1)
PYRO_2_FIRE: U16.4 (2A); also elsewhere on the board
PYRO_2_SENS: R8.1, R14.2, U15.5 (S2)
PYRO_3_FIRE: U16.9 (3A); also elsewhere on the board
PYRO_3_SENS: R17.1, R18.2, U15.10 (S3)
PYRO_4_FIRE: U16.12 (4A); also elsewhere on the board
PYRO_4_SENS: R15.1, R16.2, U15.14 (S4)
SENSE_EN: R51.1, U15.1 (SEL1), U15.4 (SEL2), U15.11 (SEL3), U15.15 (SEL4); also elsewhere on the board

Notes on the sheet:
Individual Pyro Channel Power Control
SENSE DESIGN NOTES 100k / 18k dividers: 16.8 V -> 2.563 V nominal; 2.607 V at +/-1% worst-case ratio. U15 and U7 use the MCU 3.3 V rail and common SENSE_EN; R44 holds enable low at reset. TMUX1511 powered-off isolation is specified only for signals <=3.6 V; no transient clamp is implied. 10 nF caps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
Pyro sense: powered-off isolation and ADC filtering
Pyro power good will be determined by MCU before fire command is sent
